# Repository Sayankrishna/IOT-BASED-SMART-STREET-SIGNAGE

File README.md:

View this project on [CADLAB.io](https://cadlab.io/project/29192). 

# IOT-BASED-SMART-STREET-SIGNAGE

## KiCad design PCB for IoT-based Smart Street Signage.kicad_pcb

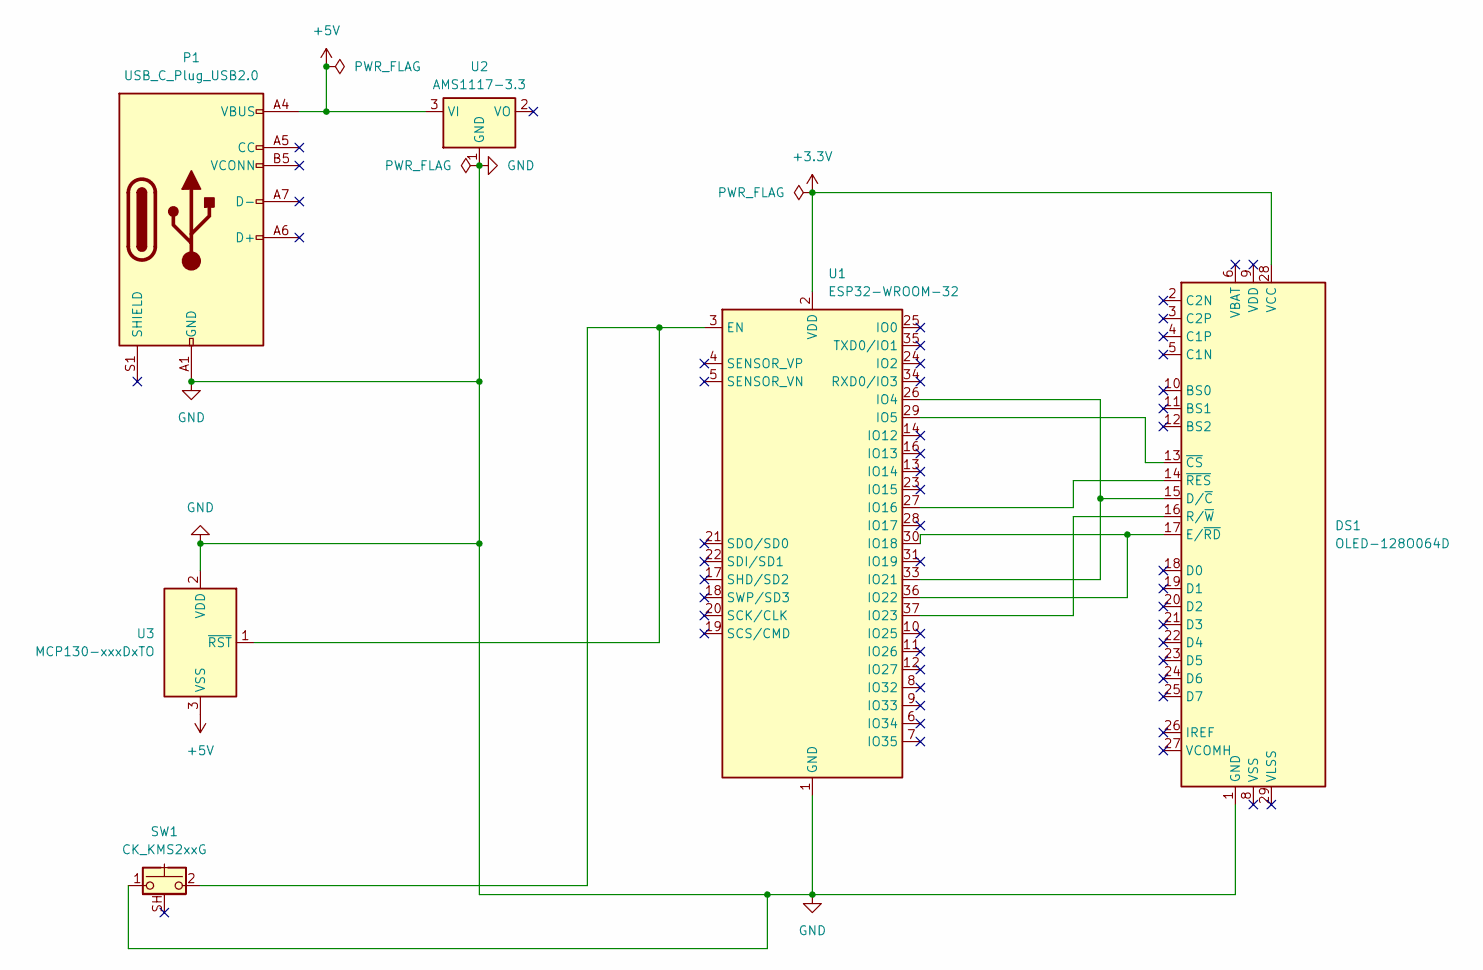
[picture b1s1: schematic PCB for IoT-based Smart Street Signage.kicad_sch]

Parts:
DS1: OLED-128O064D
P1: USB_C_Plug_USB2.0; USB_C_Plug_ShenzhenJingTuoJin_918-118A2021Y40002_Vertical
SW1: CK_KMS2xxG; SW_SPST_CK_KMS2xxGP
U1: ESP32-WROOM-32
U2: AMS1117-3.3; SOT-223-3_TabPin2
U3: MCP130-xxxDxTO; TO-92_Inline

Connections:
+3.3V: DS1.28 (VCC), U1.2 (VDD)
+5V: P1.A4 (VBUS), P1.A9 (VBUS), P1.B4 (VBUS), P1.B9 (VBUS), U2.3 (VI), U3.3 (VSS)
GND: DS1.1 (GND), DS1.30 (GND), P1.A1 (GND), P1.A12 (GND), P1.B1 (GND), P1.B12 (GND), SW1.1, U1.1 (GND), U1.15 (GND), U1.38 (GND), U1.39 (GND), U2.1 (GND), U3.2 (VDD)
unnamed: DS1.15 (D/~C), U1.26 (IO4), U1.33 (IO21)
unnamed: DS1.17 (E/~RD), U1.30 (IO18), U1.36 (IO22)
unnamed: DS1.16 (R/~W), U1.37 (IO23)
unnamed: DS1.13 (~CS), U1.29 (IO5)
unnamed: DS1.14 (~RES), U1.27 (IO16)
unnamed: SW1.2, U1.3 (EN), U3.1 (~RST)

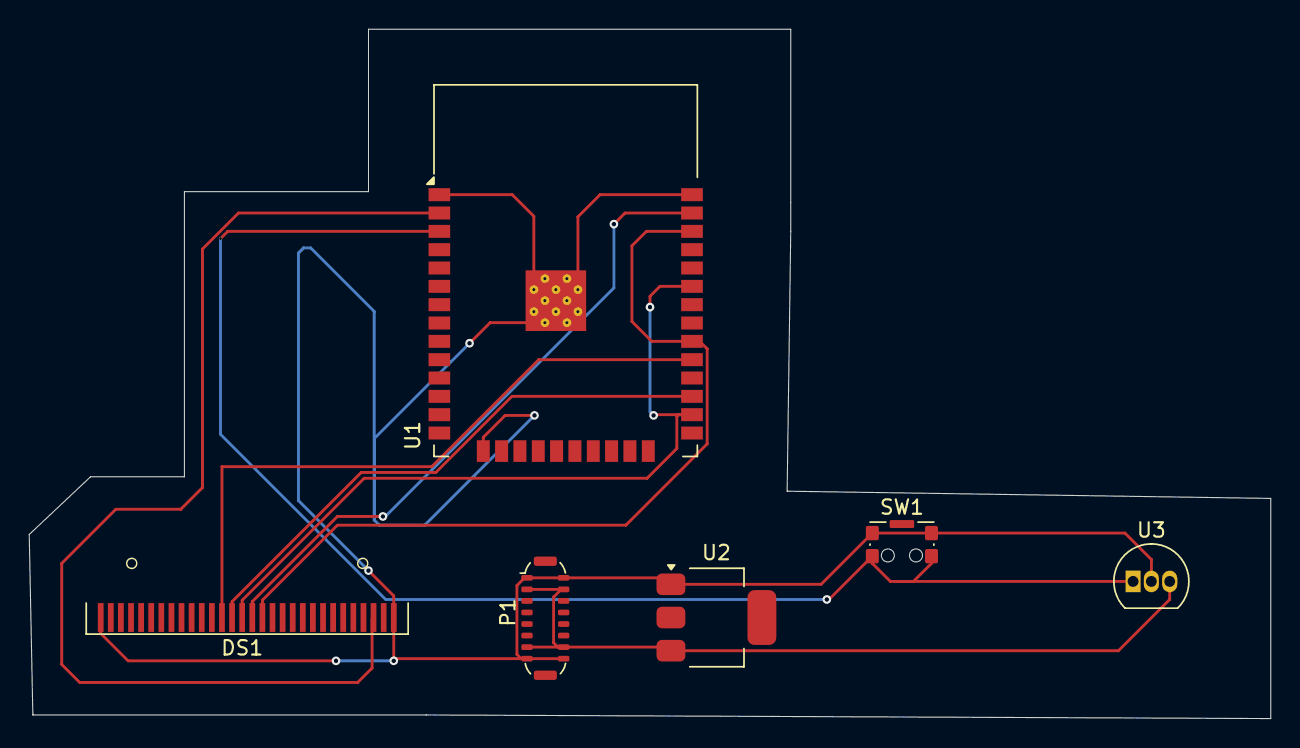
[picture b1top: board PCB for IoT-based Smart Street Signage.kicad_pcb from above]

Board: 2 copper layers, 86.0 x 47.8 mm, 6 parts (0 on the bottom side), 9 nets.

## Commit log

2025-04-07 Backlink to CADLAB.io has been added.
